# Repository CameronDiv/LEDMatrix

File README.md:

# LEDMatrix
LED matrix controlled by an Arduino that lets you make and upload pixel art.

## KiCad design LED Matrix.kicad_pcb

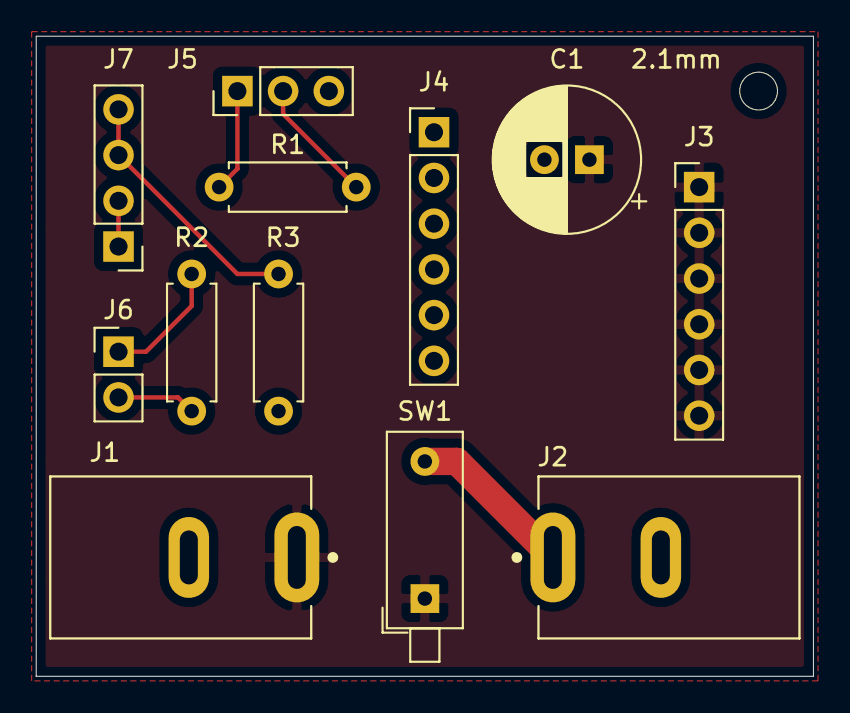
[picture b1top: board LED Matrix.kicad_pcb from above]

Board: 2 copper layers, 43.2 x 35.6 mm, 12 parts (0 on the bottom side), 9 nets.

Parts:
C1: CP; CP_Radial_D8.0mm_P2.50mm
J1, J2: PJ-037AH; CUI_PJ-037AH
J3, J4: Conn_01x06; PinHeader_1x06_P2.54mm_Vertical
J5: Conn_01x03; PinHeader_1x03_P2.54mm_Vertical
J6: Conn_01x02; PinHeader_1x02_P2.54mm_Vertical
J7: Conn_01x04; PinHeader_1x04_P2.54mm_Vertical
R1: 160; R_Axial_DIN0207_L6.3mm_D2.5mm_P7.62mm_Horizontal
R2: 330; R_Axial_DIN0207_L6.3mm_D2.5mm_P7.62mm_Horizontal
R3: 1k; R_Axial_DIN0207_L6.3mm_D2.5mm_P7.62mm_Horizontal
SW1: SW_DIP_x01; SW_DIP_SPSTx01_Piano_10.8x4.1mm_W7.62mm_P2.54mm

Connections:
GND: C1.2, J1.2, J2.2, J4.1, J4.2, J4.3, J4.4, J4.5, J4.6, J5.3, R3.2
unnamed: J2.1, SW1.2
unnamed: J5.1, R1.1
unnamed: J5.2, R1.2
unnamed: J6.1, R2.1
unnamed: J6.2, R2.2
unnamed: J7.1, J7.2
unnamed: J7.3, J7.4, R3.1
VDD: C1.1, J1.1, J3.1, J3.2, J3.3, J3.4, J3.5, J3.6, SW1.1

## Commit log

2021-07-27 Create Image Conversion (Python)
2021-07-27 Rename PictureConversion.py to Picture Conversion (Python)/PictureConversion.py
2021-07-27 Rename main.py to Picture Conversion (Python)/main.py
2021-07-27 Rename FinalMatrixV1.1.ino to Arduino Code/FinalMatrixV1.1.ino
2021-07-27 Rename LED Matrix-cache.lib to KiCAD/LED Matrix-cache.lib
2021-07-27 Create Eeschema
